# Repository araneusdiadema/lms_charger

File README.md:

# LMS Charger

## Introduction 
LMS Charger is a miniature module with USB-C designed for charging
Li-Po bateries. I designed this module while working on other projects
where I needed small Li-Po battery and available solutions were too big
for the application. I also needed some other features.

## Features
- USB-C input - for charging the battery
- MCP73833 - battery charger with selectable current up to 500mA,
  selectable resistor is used to set the current.
- Power Path - for powering the output from the USB, while the
  battery is being charged.

## Safety
 - This module was designed for Li-Po batteries with protection circuit
   inside the package, don't use with unprotected batteries. Li-Ion
   can be used, but use those with protection circuit.
 - The output of module is either 5V or VBAT, depending on whether the
   USB is connected. Connect only with electronics that can handle
   this voltage range.

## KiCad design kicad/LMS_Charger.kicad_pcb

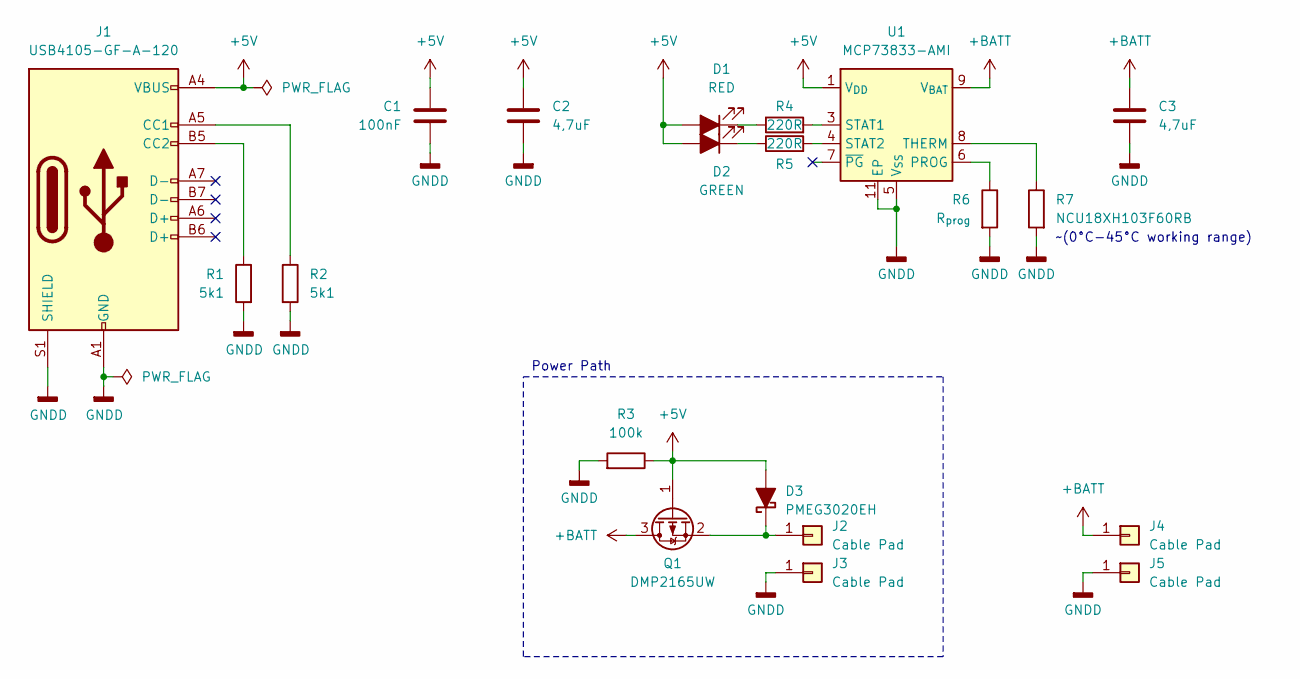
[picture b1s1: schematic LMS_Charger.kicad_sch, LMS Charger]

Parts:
C1: 100nF; C_0603_1608Metric
C2, C3: 4,7uF; C_0603_1608Metric
D1: RED; LED_0603_1608Metric
D2: GREEN; LED_0603_1608Metric
D3: PMEG3020EH; Nexperia_CFP3_SOD-123W
J1: USB4105-GF-A-120; USB_C_Receptacle_GCT_USB4105-xx-A_16P_TopMnt_Horizontal
J2, J3, J4, J5: Cable Pad; SMD_Cable_pad_1
Q1: DMP2165UW; SOT-323_SC-70
R1, R2: 5k1; R_0603_1608Metric
R3: 100k; R_0603_1608Metric
R4, R5: 220R; R_0603_1608Metric
R6: R_{prog}; R_0603_1608Metric
R7: NCU18XH103F60RB; R_0603_1608Metric
U1: MCP73833-AMI; DFN-10-1EP_3x3mm_P0.5mm_EP1.58x2.35mm

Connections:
+5V: C1.1, C2.1, D1.2 (A), D2.2 (A), D3.2 (A), J1.A4 (VBUS), J1.A9 (VBUS), J1.B4 (VBUS), J1.B9 (VBUS), Q1.1 (G), R3.1, U1.1 (V_{DD}), U1.2 (V_{DD})
+BATT: C3.1, J4.1, Q1.3 (D), U1.9 (V_{BAT}), U1.10 (V_{BAT})
GNDD: C1.2, C2.2, C3.2, J1.A1 (GND), J1.A12 (GND), J1.B1 (GND), J1.B12 (GND), J1.S1 (SHIELD), J3.1, J5.1, R1.2, R2.2, R3.2, R6.2, R7.2, U1.5 (V_{SS}), U1.11 (EP)
unnamed: D1.1 (K), R4.1
unnamed: D2.1 (K), R5.1
unnamed: D3.1 (K), J2.1, Q1.2 (S)
unnamed: J1.A5 (CC1), R2.1
unnamed: J1.B5 (CC2), R1.1
unnamed: R6.1, U1.6 (PROG)
unnamed: R4.2, U1.3 (STAT1)
unnamed: R5.2, U1.4 (STAT2)
unnamed: R7.1, U1.8 (THERM)

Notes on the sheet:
~(0°C-45°C working range)
Power Path

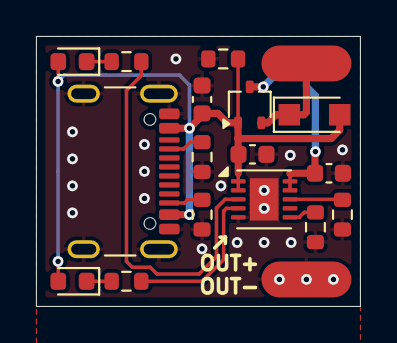
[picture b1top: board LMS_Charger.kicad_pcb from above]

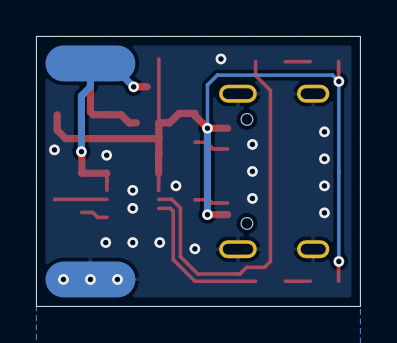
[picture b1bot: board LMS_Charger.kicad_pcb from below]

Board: 2 copper layers, 18.0 x 15.0 mm, 20 parts (2 on the bottom side), 12 nets.

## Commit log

2025-04-25 draft(kicad): Added first draft of the electronics
2025-04-25 feat(lower_current): Created light version of charger for small bateries
2025-04-25 fix(values): Minor updates in components and footprints
2025-04-25 fix(power_path): Solved problem with leaking current through reverse diode, adjusted LED resistors
2025-04-25 docs(gitignore): Modify gitignore to exclude PDF files
2025-04-25 fab(gerber): Generated gerber files for manufactiring
2025-07-02 fab(gerber): Generated gerber files for manufacturing
2025-07-02 docs(readme): Updated readme
